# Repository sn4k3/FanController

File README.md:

# FanController
 PWM fan controller using ATtiny85

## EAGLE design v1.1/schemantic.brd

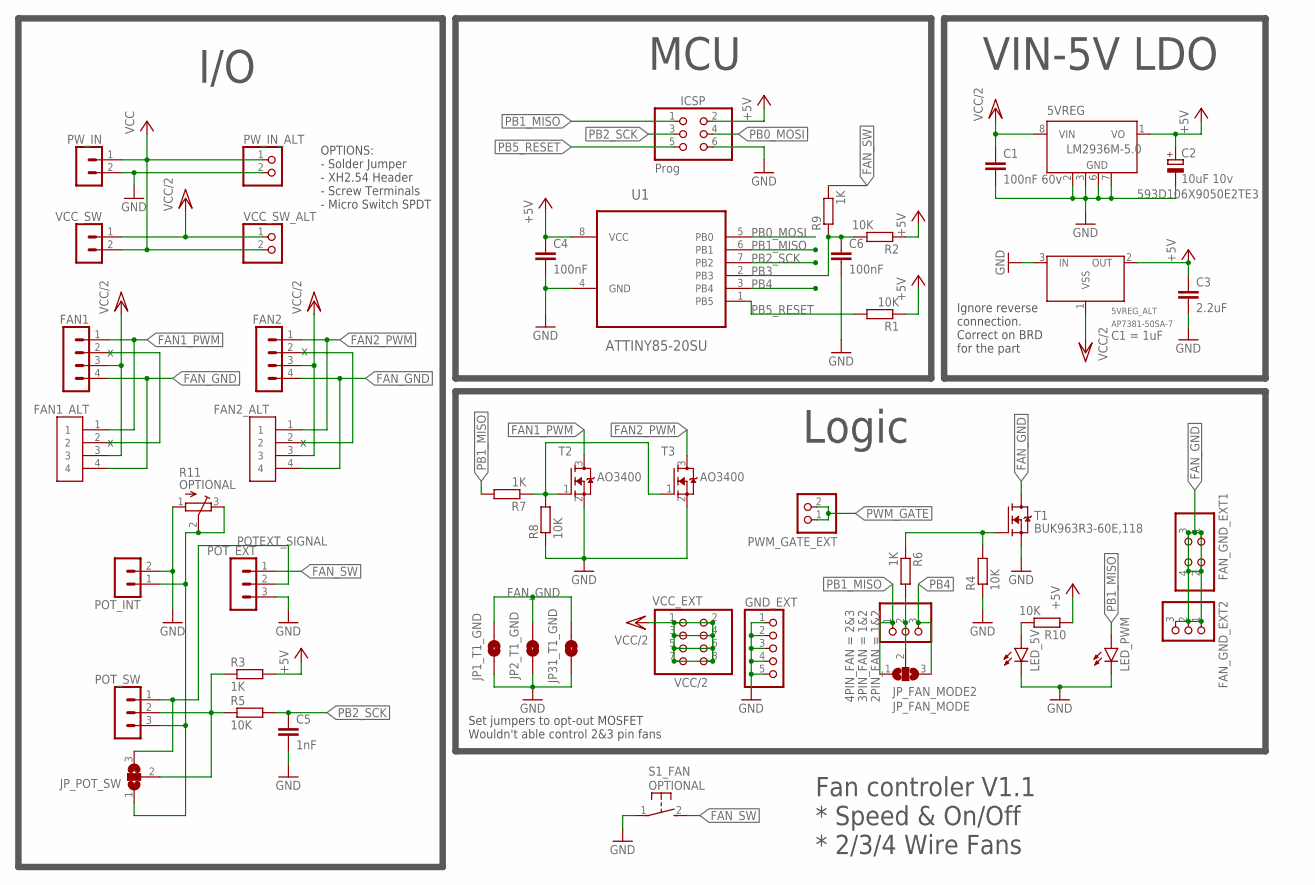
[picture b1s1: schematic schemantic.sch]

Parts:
5VREG: LM2936M-5.0; SO08; MPN LM2936HVMA-5.0/NOPB
5VREG_ALT: AP7381-50SA-7; XC6206_SOT-23
C1: 100nF 60v; C1206
C2: 10uF 10v; SMC_E
C3: 2.2uF; C0805
C4, C6: 100nF; C0805
C5: 1nF; C0805
FAN1, FAN2: FAN1; B4P-VH
FAN1_ALT, FAN2_ALT: 1X4-BIG; 1X04-BIG
FAN_GND_EXT1: PINHD-2X2; 2X02
FAN_GND_EXT2: PINHD-1X3; 1X03
GND_EXT: PINHD-1X5; 1X05
ICSP: Prog; 2X03
JP1_T1_GND, JP2_T1_GND, JP31_T1_GND: JUMPER-SMT_2_NO_NO-SILK; SMT-JUMPER_2_NO_NO-SILK
JP_FAN_MODE: DC_COM_PWM; SJ_2
JP_FAN_MODE2: PINHD-1X3; 1X03
JP_POT_SW: SJ2W; SJ_2
LED_5V: LEDCHIPLED_0805; CHIPLED_0805
LED_PWM: LEDCHIPLED_0805; CHIPLED_0805
POT_EXT: POT_EXT; B3B-XH-A
POT_INT: POT_INT; B2B-XH-A
POT_SW: POT_SW; B3B-XH-A
PWM_GATE_EXT: PINHD-1X2; 1X02
PW_IN: Power In; B2P-VH
PW_IN_ALT: PINHD-1X2; 1X02
R1, R2, R4, R5, R8, R10: 10K; R0805
R3, R6, R7, R9: 1K; R0805
R11: TRIM_EU-3223W; 3223W
S1_FAN: DTSM-3
T1: BUK963R3-60E,118; D2PAK_TO263
T2, T3: AO3400; SOT23
U1: ATTINY85-20SU; SOIC127P798X216-8N
VCC_EXT: PINHD-2X4; 2X04
VCC_SW: Power SW; B2P-VH
VCC_SW_ALT: PINHD-1X2; 1X02

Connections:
+5V: 5VREG.1 (VO), 5VREG_ALT.2 (OUT), C2.+, C3.1, C4.1, ICSP.2, R1.1, R2.1, R3.2, R10.1, U1.8 (VCC)
FAN1_LATCH: FAN1.2, FAN1_ALT.2
FAN1_PWM: FAN1.1, FAN1_ALT.1, T2.3 (D)
FAN2_LATCH: FAN2.2, FAN2_ALT.2
FAN2_PWM: FAN2.1, FAN2_ALT.1, T3.3 (D)
FAN_GND: FAN1.4, FAN1_ALT.4, FAN2.4, FAN2_ALT.4, FAN_GND_EXT1.1, FAN_GND_EXT1.2, FAN_GND_EXT1.3, FAN_GND_EXT1.4, FAN_GND_EXT2.1, FAN_GND_EXT2.2, FAN_GND_EXT2.3, JP1_T1_GND.2, JP2_T1_GND.2, JP31_T1_GND.2, T1.2 (D)
FAN_SW: POT_EXT.1, R9.2, S1_FAN.2
GND: 5VREG.2 (GND), 5VREG.3 (GND), 5VREG.6 (GND), 5VREG.7 (GND), 5VREG_ALT.3 (IN), C1.2, C2.-, C3.2, C4.2, C5.2, C6.2, GND_EXT.1, GND_EXT.2, GND_EXT.3, GND_EXT.4, GND_EXT.5, ICSP.6, JP1_T1_GND.1, JP2_T1_GND.1, JP31_T1_GND.1, LED_5V.C, LED_PWM.C, POT_EXT.3, POT_INT.2, PW_IN.2, PW_IN_ALT.2, R4.1, R8.1, R11.1 (A), S1_FAN.1, T1.3 (S), T2.2 (S), T3.2 (S), U1.4 (GND)
JP1_COM: JP_FAN_MODE.2, JP_FAN_MODE2.2, R6.2
LED1_ANODE: LED_5V.A, R10.2
PB0_MOSI: ICSP.4, U1.5 (PB0)
PB1_MISO: ICSP.1, JP_FAN_MODE.1, JP_FAN_MODE2.1, LED_PWM.A, R7.2, U1.6 (PB1)
PB2_SCK: C5.1, ICSP.3, R5.2, U1.7 (PB2)
PB3: C6.1, R2.2, R9.1, U1.2 (PB3)
PB4: JP_FAN_MODE.3, JP_FAN_MODE2.3, U1.3 (PB4)
PB5_RESET: ICSP.5, R1.2, U1.1 (PB5)
POTEXT_SIGNAL: JP_POT_SW.3, POT_EXT.2, POT_SW.1
POTINT_SIGNAL: JP_POT_SW.1, POT_INT.1, POT_SW.3, R11.2 (S), R11.3 (E)
POTSW_COM: JP_POT_SW.2, POT_SW.2, R3.1, R5.1
PWM_GATE: PWM_GATE_EXT.1, PWM_GATE_EXT.2, R7.1, R8.2, T2.1 (G), T3.1 (G)
T1_GATE: R4.2, R6.1, T1.1 (G)
VCC: PW_IN.1, PW_IN_ALT.1, VCC_SW.2, VCC_SW_ALT.2
VCC/2: 5VREG.8 (VIN), 5VREG_ALT.1 (VSS), C1.1, FAN1.3, FAN1_ALT.3, FAN2.3, FAN2_ALT.3, VCC_EXT.1, VCC_EXT.2, VCC_EXT.3, VCC_EXT.4, VCC_EXT.5, VCC_EXT.6, VCC_EXT.7, VCC_EXT.8, VCC_SW.1, VCC_SW_ALT.1

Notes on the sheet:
VIN-5V LDO
I/O
MCU
Logic
Fan controler V1.1 * Speed & On/Off * 2/3/4 Wire Fans
Ignore reverse connection. Correct on BRD for the part
Set jumpers to opt-out MOSFET Wouldn't able control 2&3 pin fans
OPTIONS: - Solder Jumper - XH2.54 Header - Screw Terminals - Micro Switch SPDT

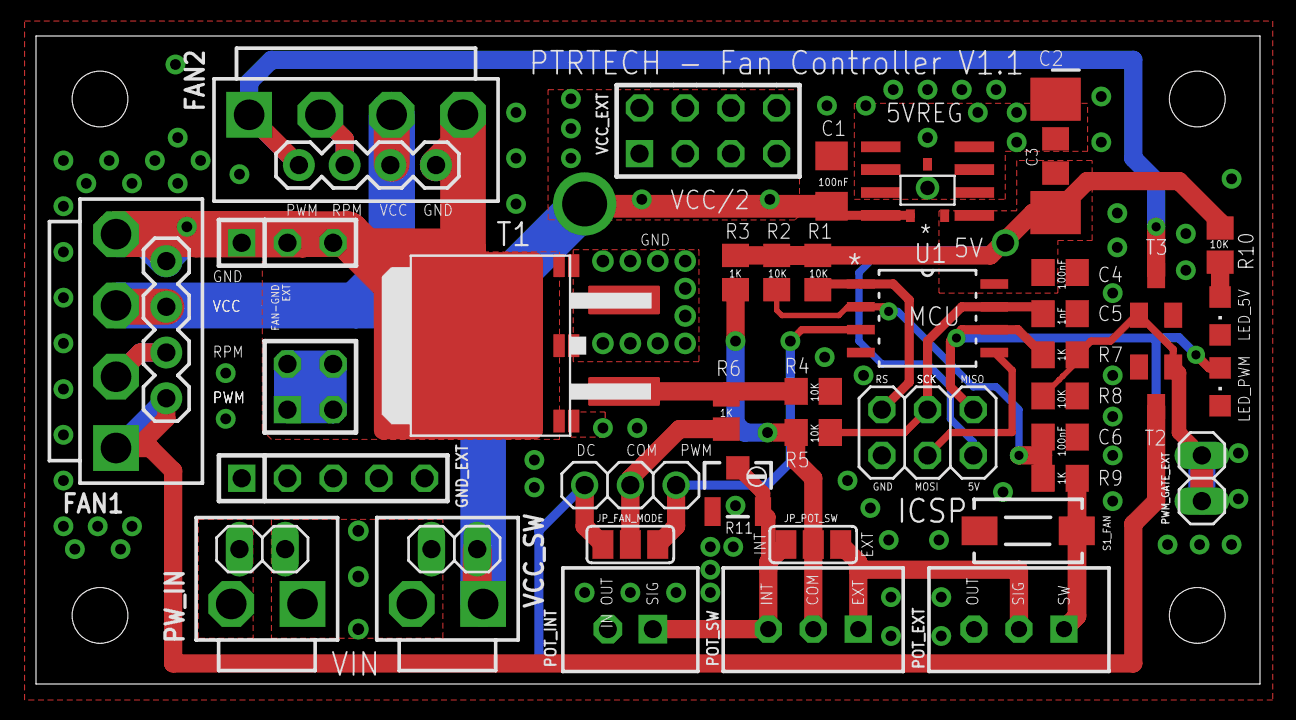
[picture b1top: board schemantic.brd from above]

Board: 2 copper layers, 68.0 x 36.0 mm, 49 parts (0 on the bottom side), 23 nets.

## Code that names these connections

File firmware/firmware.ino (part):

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 *
 *                       ATtiny25/45/85
 *                      -------u-------
 *  RST - A0 - (D 5) --| 1 PB5   VCC 8 |-- +5V
 *                     |               |
 * SWITCH A3 - (D 3) --| 2 PB3   PB2 7 |-- (D 2) - A1  --> 10K Potentiometer
 *                     |               |
 * MOSFET A2 - (D 4) --| 3 PB4   PB1 6 |-- (D 1) - PWM --> FET -> Fan PWM Wire
 *                     |               |
 *              Gnd ---| 4 GND   PB0 5 |-- (D 0) - PWM --> Disabled
 *                     -----------------
 *  https://thewanderingengineer.com/2014/08/11/pin-change-interrupts-on-attiny85/
 *
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
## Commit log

2025-07-31 Organize, add kicad convertion and fuse docs

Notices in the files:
parts and their libraries:
con-jst-vh: Copyright (C) 02/2017, kylie
SparkFun-Jumpers: Licensing: Creative Commons ShareAlike 4.0 International - https://creativecommons.org/licenses/by-sa/4.0
